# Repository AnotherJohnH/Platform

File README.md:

# PDK

PDK is a Portable Development Kit for C++ host and embedded applications. It is intended to be used as a git submodule inside application projects.

## Status

## Libraries

Embedded application support libraries

|Library|Purpose|
|-------|-------|
|[TGT](TGT)|Target support: toolchains, vector tables, linker scripts, loadable image generation, and build macros.|
|[UCL](UCL)|Small standard C library subset for embedded builds.|
|[MTL](MTL)|Bare metal support for microcontrollers: MCU bringup, clocks, UARTs, timers, I2C, SPI etc.|
|[TNY](TNY)|Additional standard C library support dependent on `MTL` for I/O.|
|[HWR](HWR)|Hardware configuration layer for reusable board/product APIs and native simulation variants.|

General purpose libraries for host and embedded applications

|Library|Purpose|
|-------|-------|
|STB|Static data structures and utility types for limited-memory code.|
|USB|USB descriptors and support utilities.|
|SIG|Signal processing and synthesis.|
|MIDI|MIDI protocol support.|
|GUI|Simple GUI and 2D rendering.|
|TRM|Lightweight terminal/curses-style interface.|

Host OS abstraction libraries

|Library|Purpose|
|-------|-------|
|PLT|Platform abstraction for display, MIDI, audio etc.|

## Starting a new project using the PDK

Create a new **git** project directory and add the **PDK** as a git submodule.

```
mkdir MyProject
cd MyProject
git init .
git submodule add https://github.com/SloeComputers/PDK.git
cd PDK
make template
```

The project template installer should run..

```
Project dir [/Users/fred/MyProjects] : <project root directory>
Copyright owner [John D. Haughton] : <copyright owner>
Copyright year [2017] : <copyright year>
User name [SloeComputers] : <GitHub user id>
Application [MyProject] : <name of application>
Version [0.0.0] : <initial version>
Description [Example application] : <application purpose>
Binary [foo] : <filename of application binary>

Install 'CMakeLists.txt' to '<project root directory>'
Install 'LICENSE' to '<project root directory>'
Install 'Makefile' to '<project root directory>'
Install '<filename of application binary>.cpp' to '<project root directory>/Source'
Install 'CMakeLists.txt' to '<project root directory>/Source'
Install 'README.md' to '<project root directory>'
Install '.gitignore' to '<project root directory>'
Install '_config.yml' to '<project root directory>'
Install '.clang-format' to '<project root directory>'
Install 'build_on_push.yml' to '<project root dir>/.github/workflows'
```

Add the newly instantiated project as an initial git patch then build.

```
cd ..
git add .
git commit -m Initial
make
```

Run the example application just built. (Try with -v and -h too)

```
build/native/Source/myproject
Hello, world!
```

The following small projects are using the PDK...
* [MineSweeper](https://github.com/SloeComputers/MineSweeper/)
* [Sternhalma](https://github.com/SloeComputers/Sternhalma/)
* [Zif](https://github.com/SloeComputers/Zif/)

### Linux

One of the primary target platforms.

Depend on SDL2, so a development install of SDL2 is required.

Typically the following packages will be required...

```
sudo apt-get install cmake
sudo apt-get install libsdl2-dev
```

### macOS

One of the primary target platforms.

Depend on SDL2, so a development install of SDL2 is required.

Typically the following packages will be required...

```
brew update
brew install cmake
brew install sdl2
```

### Kindle3

Although this is also a Linux build, it does not depend on SDL2.

Requires gcc/g++ built for arm-linux-gnueabihf targets that supports C++11 and a set of
headers and static runtime libraries that are compatible with the Linux kernel v2.6.26
installed on the Kindle3.

#### Using a Raspberry Pi as a build machine for Kindle3

The original ARMv6 Raspberry Pi running a Debian based Linux has been found to be suitable
platform to build for Kindle3. But this is far easier if an old version of Rasbian (Wheezy)
is used to ensure that libc is compatible with the old kernel on the Kindle.

Other packages required...

```
sudo apt-get install cmake
sudo apt-get install g++-4.7
```

### Browser (via Emscripten)

Uses the SDL2 library supplied with Emscripten.

### iOS

Requires access to a source installation of SDL2 which is built into a linSDL2.a as part of
the application build process.

Build of an actual app has not been achieved yet, and may not be easily achievable without
an Xcode project file.

### Android

Requires an NDK installation. Currently builds as a console only app as an integration with
an Android build of SDL2 has not been achieved yet.

## Coding style

The source is C++ but has the following non-typical for modern C++ features ...

* Memory is mostly statically or stack allocated in preference to new/delete
* Very limited STL usage
* Use of C style stdio API
* In some places have re-invented the wheel avoiding functionality that is in standard libraries
* Refer to [STYLE.md](STYLE.md) and the repository `.clang-format` for specific naming and formatting preferences.

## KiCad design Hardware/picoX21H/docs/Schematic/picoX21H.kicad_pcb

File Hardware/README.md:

# Hardware

## Configs

| Config | Docs   | Description |
|--------|--------|-------------|
| picoX7 | [README](blob/main/picoX7) | MIDI synthesizer with DAC, 16x2 LCD and 2x7 segment LED |
| picoX21H | [README](blob/main/picoX21H) | MIDI synthesizer with DAC, 16x2 LCD and an actual Yamaha YM2151 FM synthesizer chip. |
| picoSense | [README](blob/main/picoSense) | E-paper or LCD with I2C sensor. |
| picoGame | [README](blob/main/picoGame) | LCD with some buttons. |
| blinky | [README](blob/main/blinky) | Single LED. |

## Checkout

This repo uses git sub-modules, so checkout using --recurse-submodules to clone
all the dependent source...

    git clone --recurse-submodules https://github.com/SloeComputers/Hardware.git

or

    git clone --recurse-submodules ssh://git@github.com/SloeComputers/Hardware.git

## Software dependencies

+ https://github.com/SloeComputers/Platform
+ arm-none-eabi-gcc
+ cmake via UNIX make or auto detection of ninja if installed
+ Python3
+ SDL2 (only for native test target)

## Starting a new project using Hardware

```
mkdir MyProject
cd MyProject
git init .
git submodule add git@github.com:SloeComputers/Hardware.git
git submodule update --init --recursive
```

## Build

Being developed on MacOS but should build on Linux too.

Indirect build for supported targets, rp2040 and rp2350 with cmake and make (or ninja)...

    make

Build a single hardware target e.g. rp2350 using cmake...

    mkdir build
    cd build
    cmake -DCMAKE_BUILD_TYPE=Release -DPLT_TARGET=rp2350 -DCMAKE_TOOLCHAIN_FILE=Platform/MTL/rp2350/toolchain.cmake ..
    make

flashable test images will be found under the build sub-directory here...

    build/Source/picoX7Test_RPIPICO_I2S_DAC.uf2

## License

This project is licensed under the MIT License - see the [LICENSE](LICENSE) file for details

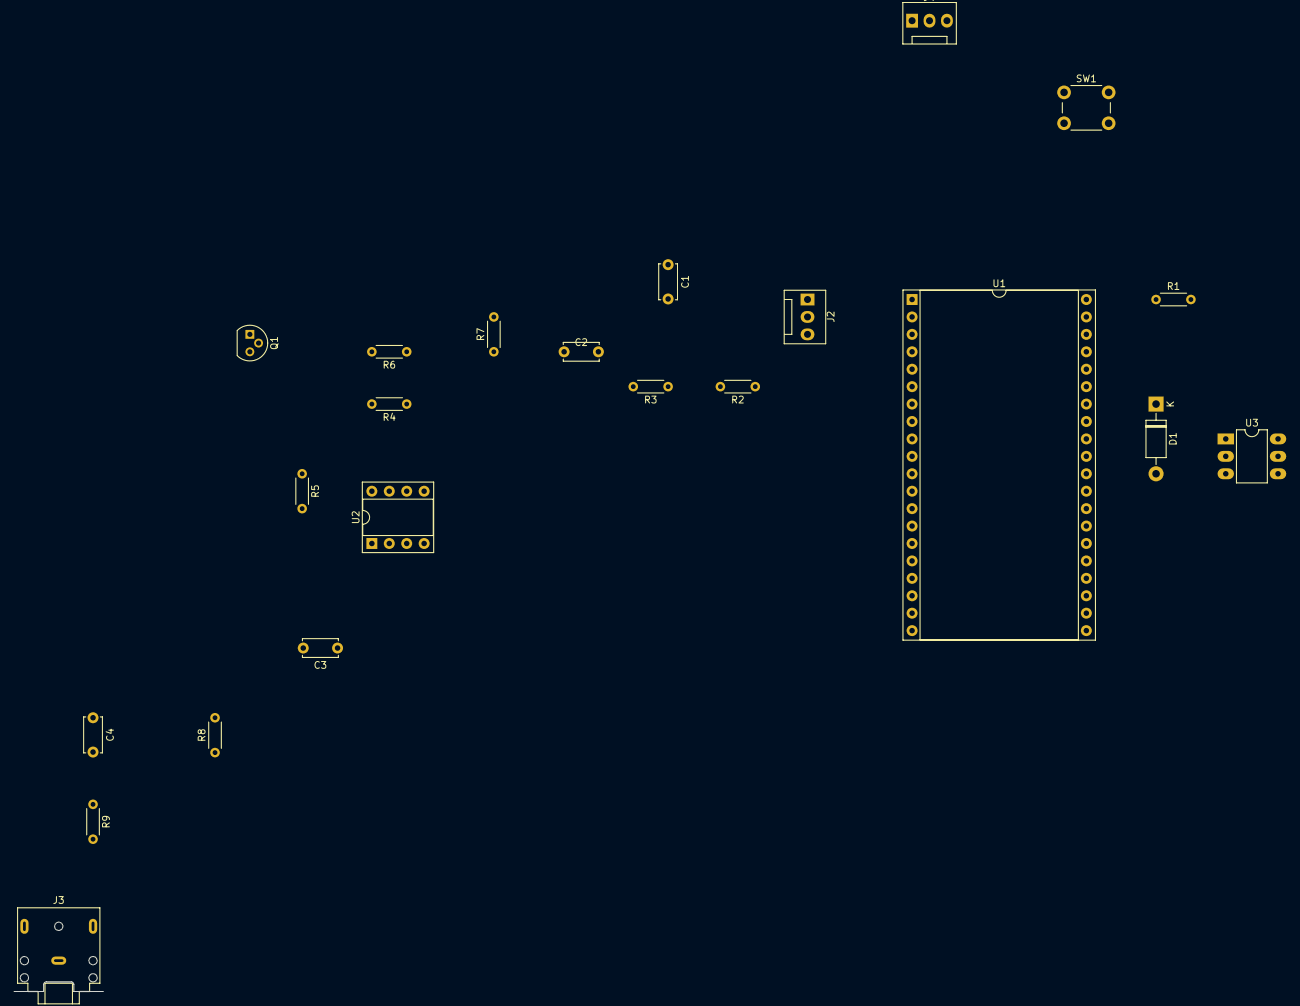
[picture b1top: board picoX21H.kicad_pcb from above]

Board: 2 copper layers, 22 parts (0 on the bottom side), 22 nets, no tracks yet.

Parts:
C1, C4: 22nF; C_Disc_D5.0mm_W2.5mm_P5.00mm
C2: 220pF; C_Disc_D5.0mm_W2.5mm_P5.00mm
C3: 1nF; C_Disc_D5.0mm_W2.5mm_P5.00mm
D1: 1N4001; D_DO-41_SOD81_P10.16mm_Horizontal
J2, J4: Debug; FanPinHeader_1x03_P2.54mm_Vertical
J3: Stereo line out; Jack_3.5mm_CUI_SJ1-3523N_Horizontal
Q1: 2N2222A; TO-92
R1: 220; R_Axial_DIN0204_L3.6mm_D1.6mm_P5.08mm_Horizontal
R2, R4, R9: 33k; R_Axial_DIN0204_L3.6mm_D1.6mm_P5.08mm_Horizontal
R3: 27k; R_Axial_DIN0204_L3.6mm_D1.6mm_P5.08mm_Horizontal
R5: 220k; R_Axial_DIN0204_L3.6mm_D1.6mm_P5.08mm_Horizontal
R6: 1.8k; R_Axial_DIN0204_L3.6mm_D1.6mm_P5.08mm_Horizontal
R7: 47k; R_Axial_DIN0204_L3.6mm_D1.6mm_P5.08mm_Horizontal
R8: 2.2k; R_Axial_DIN0204_L3.6mm_D1.6mm_P5.08mm_Horizontal
SW1: RST; SW_PUSH_6mm_H5mm
U1: Pico 2 (RP2350); DIP-40_W25.4mm_Socket
U2: TL072; DIP-8_W7.62mm_Socket
U3: H11L1; DIP-6_W7.62mm_LongPads

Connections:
+3V3: U1.36 (3V3), U3.6
+5V: U1.39 (VSYS), U1.40 (VBUS)
/MIDI 31250 baud 8-N-1: U1.27 (GPIO21), U3.4
/console GND: J2.3, U1.3 (GND)
/console RX: J2.2, U1.2 (GPIO1)
/console TX 115200 baud 8-N-1: J2.1, U1.1 (GPIO0)
Earth: C1.1, R7.2, SW1.2, U2.3 (+), U2.5 (+), U3.5
unnamed: C1.2, R2.2, R3.1
unnamed: C2.2, R6.1, R7.1
unnamed: C3.2, C4.1, R8.2, U2.1
unnamed: C4.2, R9.1
unnamed: D1.2 (A), U3.2
unnamed: D1.1 (K), R1.1, U3.1
unnamed: J3.T, R9.2
unnamed: Q1.2 (B), R6.2
unnamed: Q1.3 (C), R8.1
unnamed: C3.1, Q1.1 (E), R5.2, U2.2 (-)
unnamed: R4.2, R5.1, U2.7
unnamed: C2.1, U1.4 (GPIO2)
unnamed: R2.1, U1.5 (GPIO3)
unnamed: SW1.1, U1.30 (RUN)
unnamed: R3.2, R4.1, U2.6 (-)

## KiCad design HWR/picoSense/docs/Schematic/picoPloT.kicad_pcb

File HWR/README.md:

# HWR - Hardware library

The HWR library enables projects with similar hardware requirements to share common C++ APIs, allowing rapid development of new projects and portability of a project codebase between different hardware variants.

The library also supports native variants for macOS and Linux targets, where physical hardware I/O is simulated for debugging and quick evaluation.

## Configs

| HWR_CONFIG             | Platform I/O |
|------------------------|--------------|
| [blinky](blinky)       | Single LED   |
| [picoX7](picoX7)       | MIDI synthesizer with DAC, 16x2 LCD and 2x7 segment LED |
| [picoX21H](picoX21H)   | MIDI synthesizer with DAC, 16x2 LCD and an actual Yamaha YM2151 FM synthesizer chip. |
| [picoSense](picoSense) | E-paper or LCD with I2C sensor. |
| [picoGame](picoGame)   | LCD with some buttons. |

## Usage

The hardware config for a project is selected in the top level `CMakeLists.txt` before the `PDK` sub-directory is added.

```cmake
set(HWR_CONFIG picoX7)

add_subdirectory(PDK)
```

the C++ APIs are then accessible in the project source with:

```cpp
#include "HWR/picoX7/Config.h"
```

The cmake build targets for the config are then defined using the CMake helper for the selected config:

```cmake
add_picoX7_executable(picoSynth
                         picoSynth.cpp
                      LIBRARIES
                         Acorn
                         Casio
                         Roland
                         Experiment)
```

this will build all available variants for the current target including test images.

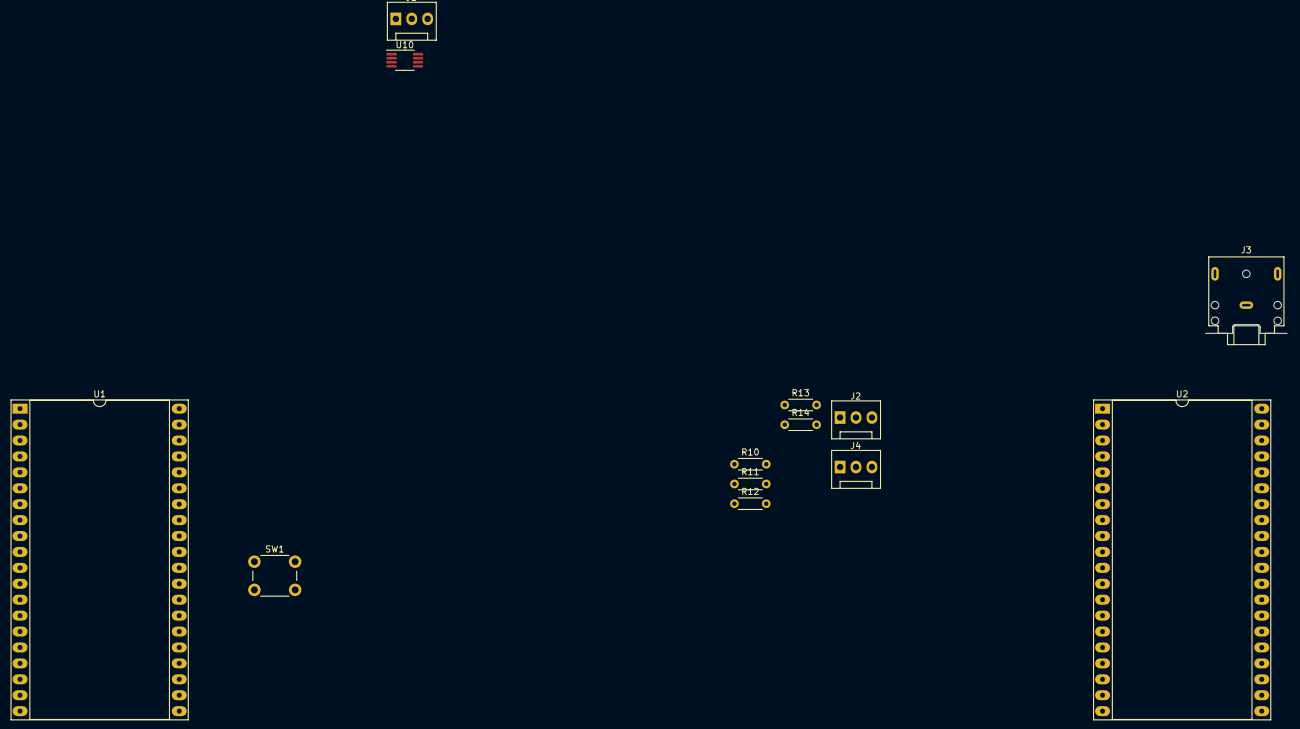
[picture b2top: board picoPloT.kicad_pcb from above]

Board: 2 copper layers, 13 parts (0 on the bottom side), 8 nets, no tracks yet.

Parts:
J1, J2, J4: Debug; FanPinHeader_1x03_P2.54mm_Vertical
J3: Stereo line out; Jack_3.5mm_CUI_SJ1-3523N_Horizontal
R10, R11, R12, R13, R14: 330; R_Axial_DIN0204_L3.6mm_D1.6mm_P5.08mm_Horizontal
SW1: RST; SW_PUSH_6mm_H5mm
U1: MCU arm Cortex-M0x2; DIP-40_W25.4mm_Socket_LongPads
U2: I2S DAC; DIP-40_W25.4mm_Socket_LongPads
U10: MCP9808; MSOP-8_3x3mm_P0.65mm

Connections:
/console (RX) 115200 baud 8-N-1: J1.2, U1.2 (GPIO1)
/console (TX) 115200 baud 8-N-1: J1.1, U1.1 (GPIO0)
Earth: SW1.2, U2.3 (GND), U2.8 (GND), U2.13 (GND), U2.18 (GND), U2.23 (GND), U2.28 (GND), U2.33 (GND), U2.38 (GND), U10.4 (GND)
unnamed: J1.3, U1.3 (GND)
unnamed: J4.2, U1.23 (GND)
unnamed: J4.3, U1.22 (GPIO17)
unnamed: SW1.1, U1.30 (RUN)
unnamed: U1.39 (VSYS), U2.39 (VSYS)

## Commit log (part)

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2023-06-18 Add MIDI::Interface (and adapt mbed LPC1768 UART to support)
2023-06-22 Fix RPiPico UF2 generation bug - was miscomputing the load address
2023-07-02 Add MTL_gectch_empty()
2023-07-03 Add SysEx support to the new MIDI classes
2023-07-05 Fix some target builds which don't seem to have PRId64 or PRIx64
2023-07-15 STB Updates to new MIDI classes + improved channel mode support
2023-07-17 RP2040: Add some buffered IRQ driven I/O
2023-07-23 Properly expose vprintf()
2023-07-23 Fix header filename case bug
2023-08-02 Clearer and more complete MIDI interface + include bug fix for channel pressure
2023-09-03 Add MTL 7-seg LED "driver"
2023-09-03 Some 7 seg LED tidy up
2023-09-04 Add 1602 style LCD support to MTL
2023-09-05 RPiPico implement a simple sleep() and usleep()
2023-09-07 rp2040: Fix MTL_clock() and MTL_us_clock() and switch MTL::Lcd to use usleep()
2023-09-08 Add rp2040 ADC support
2024-01-19 Add support for WaveShare 2.13" E-paper (V3)
2024-01-21 Add GUI::Canvas support for E-Paper displays
2024-01-23 RP2040 RTC
2024-01-23 Add (unsafe!!!) snprintf
2024-01-28 rp2040: PadsBank allow more than flag at a time
2024-01-28 rop2040: Tidy SPI class
2024-02-05 Fix for usleep()
2024-02-16 Add pico RTC alarm
2024-02-23 Add RP2040 PWM peripheral support
2024-02-23 Working ST7789V LCD driver for RPiPico
2024-02-24 Re-code EPaper GUI::Canvas support
2024-02-24 Update ST7789V driver
2024-02-25 Rename MCP9808 temp sens header
2024-03-02 Add fixed allocation vector
2024-06-05 RP2040: PioI2S - Add support for swapping order of clock pins
2024-06-05 RP2040: PioAudio - Add support for swapping order of clock pins and no MCLK
2024-06-05 RP2040: Allow MT_putch() redefinition by application
2024-06-07 Rename MTL/Lcd.h as it was too vague
2024-06-08 MTL: Debug helper logReg()
2024-06-11 rp2040: Initial USB device-mode implementation
2024-06-14 MTL: More work on USB-MIDI
2024-06-14 MTL: USB dynamic allocation of end-point addresses
2024-06-16 Usb types some tidy up (no functional change)
2024-06-17 MTL: RP2040 support long config decriptor lists
2024-06-17 MTL: Small tidy of USB MIDI header
2024-06-17 MTL USB MIDI fix for Jack descriptor
2024-06-19 MTL: USB Improvements to (compiled out) debug
2024-06-19 MTL USB - go back to one EP addr per EP!
2024-06-22 Refecator the USB headers
2024-07-06 Remove some unnecessary PLT v MTL differences
2024-07-06 MIDI Interface fix MT bug
2024-07-08 RP2040 add mutex implementation using the SIO spinlock registers
2024-07-10 RP2040 Fix (ammusingly broken) mono PioI2S
2024-07-11 rp2040: Initial support for starting the scond core
2024-07-13 rp2040: PioAudio use IRQ flag to identify ping/pong buffer - the ping_pong bool and the IRQswere getting out of sync when busy
2024-07-19 rp2040: harden PioAudio operation
    - Resetting the DMA read reg was being performed in the IRQ
    handler which means that if the IRQ handler fails to run
    in time the DMA will spool any old rubish that follows
    out the I2S!
    + Fixed by using twp extra DMA channels to reset the read
    reg
2024-08-24 badger2040 initial support
2024-08-24 EPaper - recode X/Y swap to be more logical
2024-08-25 Move odd refresh behaviour into Waveshre EPaper driver
2024-08-25 badger2040 I2C declaration
2024-08-25 UC8151 EPaper update
2024-08-27 Add some RP2350 peripherals
2024-08-27 Some minor tidy of RP2040
2024-08-31 RP2350: Some clock fixes
2024-09-05 Fix iHexToUF2 and usage for RP2040
2024-09-05 RP2040 and RP2350 fix for I2C0 GPIO allocation
2024-09-06 RP2040/2350 Adc updates with some extra badger2040 constants
2024-09-07 Some minor RP2350 updates
2024-09-08 Complete and fix AlphaNumLCD_I2C
2024-09-09 Initial MIDI support for Linux
2024-09-10 RP2xxx rename Uart classes with external pin numbers
2024-09-11 Some RP2xxx PWM fixes and tidy
2024-09-15 RP2350: Some DMA fixes
2024-09-23 RPPico Factor common audio streaming framework into a base class
2024-09-26 RP2xxx: Some PIO improvements
2024-09-27 rp2xxxx: PIO PWM
2024-10-01 Untested AlphaNumLcd_I2CBridge driver
2024-10-04 Extend timings for 16x2 LCD with I2C bridge
2024-10-26 MTL target config clock freq literal => unsigned
2024-10-27 Add MTL::USBMidiDevice class
2024-11-09 Update default Pcio PWM freq to system frequency
2024-11-17 Fix some header dependency issues
2024-11-24 Fix broken strcmp() !!@#@
2024-12-08 Remove dependency on googltest and replace with STB/Test.h
    also bumped C++ standard to C++17 to bring in missing operator<<
    overload for basic_ostream
2024-12-08 Reimplement STB::Heap using STB::List
2024-12-08 Fix silly mistake ion STB::List::back()
2024-12-10 Add a missing stdio.h declaration
2024-12-15 Add operator[] for STB::List
2024-12-15 Add std::clamp to TNY
2024-12-15 Apply C++17 to host project too
2024-12-15 Add const begi and end for TNY std::array
2024-12-24 Native Audio: Configurable buffer size
2025-01-03 Add voice allocation implementation to MIDI::Instrument
2025-01-03 Avoid a (false positve) warning with gcc
    + tidy some CMake warnings
2025-01-03 Reduce PLT/Midi.h include dependencies
2025-01-03 Further cmake fixes when use as a nested module
2025-01-03 refactor build directories
2025-01-04 Some tidy up for newer gcc
2025-01-05 Avoid gcc warning about a templated packed structure
    Seen in at least gcc 14. Code still seems to work ok
    but not fully tested!!
2025-01-12 RPiPico: Add Pull up option for UART rx
2025-01-14 Remove MTL_load call from reset vector for all arm targets
2025-01-19 Fix over greedy SYSEX handling in MIDIinterface
    - could read the input FIFO without checking for empty
    leading to SYSEX corruption
2025-01-24 Extra STB list insert method
2025-01-25 Fix broken assert
2025-01-29 Support for raw MIDI via MIDI::Interface
2025-03-05 Add EXPECT_LT and EXPECT_GT to STB/Test.h
2025-03-10 STB/test.h support use of EXPECT_.. outside scope of test
2025-03-12 Add Pimoroni tiny2350 as a build target
2025-03-18 Fix for RaspPi PIO to allow both ISR and OSR to be configured
2025-03-22 MIDI::Instrument expose NUM_VOICES as a const
2025-04-12 Some extra PIO peripherals for rp2xxx
2025-04-13 Re-order pins for PioYMDAC to make layout easier
2025-04-22 Move to C++20
    To get floating point template params
2025-04-24 Fix SDL2 integration
2025-04-24 Avoid C++20 volatile warning on pico builds
    - The gcc warning for deprecated volatile use is over zealous
2025-05-10 Move memset and memcpy into libMTL to avoid cicular dependency from implicit calls
2025-05-11 Fix potential crash in MIDIInterface
2025-05-22 USB updates
    = More FAT16 implementation => starting to work
    + Merge USB Device and Config classes
    => Now only none config supported
2025-05-22 USN: Tidy setup request handling
2025-05-22 Re-code USB MIDI interface for composite devices
2025-05-23 Refactor FileSystem read/write interface
2025-05-23 Some FAT16 improvements
2025-05-23 Tidy USB mass storage bukld and run
2025-05-23 FAT16 support file export
2025-05-25 Fix broken UART and I2C pad config for RP2350
2025-05-25 Fix some minor build script anoyances
2025-05-28 RP2350: Improved fault handling
2025-05-31 MTL: Add some include dependencies for rp2xxx
2025-06-06 Add autogen_py function
2025-06-08 Remove duplcicate snprintf
2025-06-08 Fix static re-constyruct bug provide proper implemenattion of _cxa guard
2025-07-01 Fix endian multi-defs
2025-07-01 PHY header updates
2025-07-02 Fix FAT16 unit test
2025-07-02 Fix up some GUI and TRM tests
2025-07-20 Modernize some GUI classes
2025-07-21 Move GUI/Colour.h
2025-07-21 Move GUI/Layout.h
2025-07-21 Split out symbol as it's own widget
2025-07-22 More GUI updates
2025-08-13 GUI: Some slider widget updates
2025-09-20 Fix minor link warning
2025-09-20 Some coding style updates
2025-09-21 Remove old style include guards
2025-09-21 Simplify some copyright notices
2025-10-05 Only buid PLT tests for native
2025-10-10 Update PioAudio for PioClock changes
2025-10-10 Allow GUI lib usage in MTL targets
2025-10-12 Add MIDIconst.h
2025-10-16 Improve pin config reporting support
2025-10-20 Add a fault handler for rpipico targets
2025-10-20 Remove some duplicate definition hazards
2025-11-03 Expose some E-paper pins
2025-11-06 Add text LCD font
2025-11-12 Add GPIO IRQ support (rp2040 and rp2350)
2025-11-12 Some tufty2040 fixes and additions
2025-11-15 Rename rpipico targets using the chip name
2025-11-17 Refactor MTL LPC11U24 builds
2025-11-17 Refactor MTL LPC1768 builds
2025-11-18 Refactor LPC810 and LPC1114 builds
    Untested
2025-11-21 Refactor nRF52 build
2025-11-22 Add is_const to python table gen
    Useful for MCUs where RAM based lookup tables are much
    faster than FLASH (RP2040 and RP2350)
2025-12-02 Add VFP support for RP2350
2025-12-21 Implement expf()
2025-12-27 TNY: Convert LF to LF+CR for stdout
2025-12-28 TNY Update getchar() to convert CR to LF
2026-01-04 Bring in SIG library from picoSynth so it can be shared
2026-01-11 Enable FP support in printf
2026-01-11 Add SIG::DualBiQuad filter
2026-01-18 Add SIG Slews
2026-01-24 Some SIG improvements
2026-01-25 SIG: Expose note to phase delta lookup in SIG.h
2026-01-31 Fix SIG:DelayN bug
2026-02-07 SIG: Add ping-pong buffers for coefficients
2026-02-07 Add SIG::DelayV
2026-02-10 Add start of clipping support
2026-02-15 SIG::Filter updates
2026-02-24 TNY - add powf and logf
2026-03-01 Add SIG::LogPot
2026-03-02 Add psuedo CV control to SIG::Osc
2026-03-06 Fix for SIG::gain constness
2026-03-08 Move github account name to SloeComputers
2026-03-08 Some fixes for picoGame hardware
2026-03-10 Update USB vendor ID to 0x510e
2026-03-11 Clean some broken links
2026-03-15 Move MIDI files into MIDI dir
2026-03-15 Rename MIDI files
2026-03-15 Add MIDI controller constants
2026-03-19 Some MIDI updates
2026-03-21 Rename Hardware directory
2026-03-22 Add some docs
2026-03-22 Doc update
2026-03-26 More docs
2026-04-02 Add WaveTable Osc to SIG
2026-04-02 Tidy SIG::Osc::WaveTable
2026-04-12 SIG: Add some unit tests and an FP64 build
    + some general quality improvements
2026-04-12 More SIG unit tests
2026-04-13 Rename some SIG dirs and namespaces
2026-04-14 STB: Complete fixed-point implementation
2026-04-14 Start move from Platform to PDK
2026-04-14 Some bug fixes
2026-04-14 More Platform => PDK changes
2026-04-19 Rename PLT_ biuild vars to PDK_
2026-04-19 Simplify build.make
2026-04-19 Some cmake fixes
2026-04-21 Re-code peoject template via python
2026-04-21 Fix Linux build
2026-04-21 HWR Fix out of bounds bug
2026-04-21 Disable SIG_FX32 as currently broken
2026-04-21 SIG fix for compare type mismatch
2026-04-22 More test fixes
2026-04-22 Fix for docs gen
2026-04-22 Try a different fix for STB/BitArray
2026-04-22 Misc temnplate and README updates
2026-04-22 Fix broken template _config.yml
2026-04-25 Fudge MTL/ConfigBase.h for now to see if UCL fixes things
2026-04-25 Further fixes
2026-04-25 Fix C header search
2026-04-26 Add <limits> header
2026-04-26 Add basic type_traits to UCL
2026-04-26 Rename .hex output as .hx in rp MTL targets
2026-04-26 Fix support for tiny2350
2026-04-26 Some nRF52 fixes
2026-04-26 Some ATtiny tidy up (not sure if it's going anywhere)
2026-04-26 Start HWR picoX7 support for tiny2350
2026-04-27 Some UCL updates
2026-04-28 Create a TGT library to host the vector table
2026-04-28 Simplify toolchain.cmake usage
2026-04-28 Add rp2350 module support to picoSense HW config
2026-04-29 Avoid some test runner builds on non native builds
2026-04-30 Start to reduce MTL directory depth
2026-05-01 Move some TNY code to UCL
2026-05-01 Move some TNY code to TGT
2026-05-03 Minor update to rp2350 Spi
2026-05-03 Some very important UCL fixes !!!
2026-05-04 Small fix to HWR template
2026-05-04 Group C-library source into subdirs by header
2026-05-05 Fix for printf/sprintf confusion bug
2026-05-05 Further refactor of TGT cmake
2026-05-06 Remove circular cmake dependency for TGT
2026-05-06 Some UCL/TNY updates
2026-05-06 Refactor MTL
2026-05-08 Tidy vector tables
2026-05-10 Some TGT and UCL tidy up
2026-05-10 Some TGT updates
2026-05-10 Fault handler
2026-05-13 Fix M0/M3 tick timer and fault handling
2026-05-14 Mid refactor fix up
2026-05-17 Some ATtiny build fixes
2026-05-17 More robust MTL_halt
